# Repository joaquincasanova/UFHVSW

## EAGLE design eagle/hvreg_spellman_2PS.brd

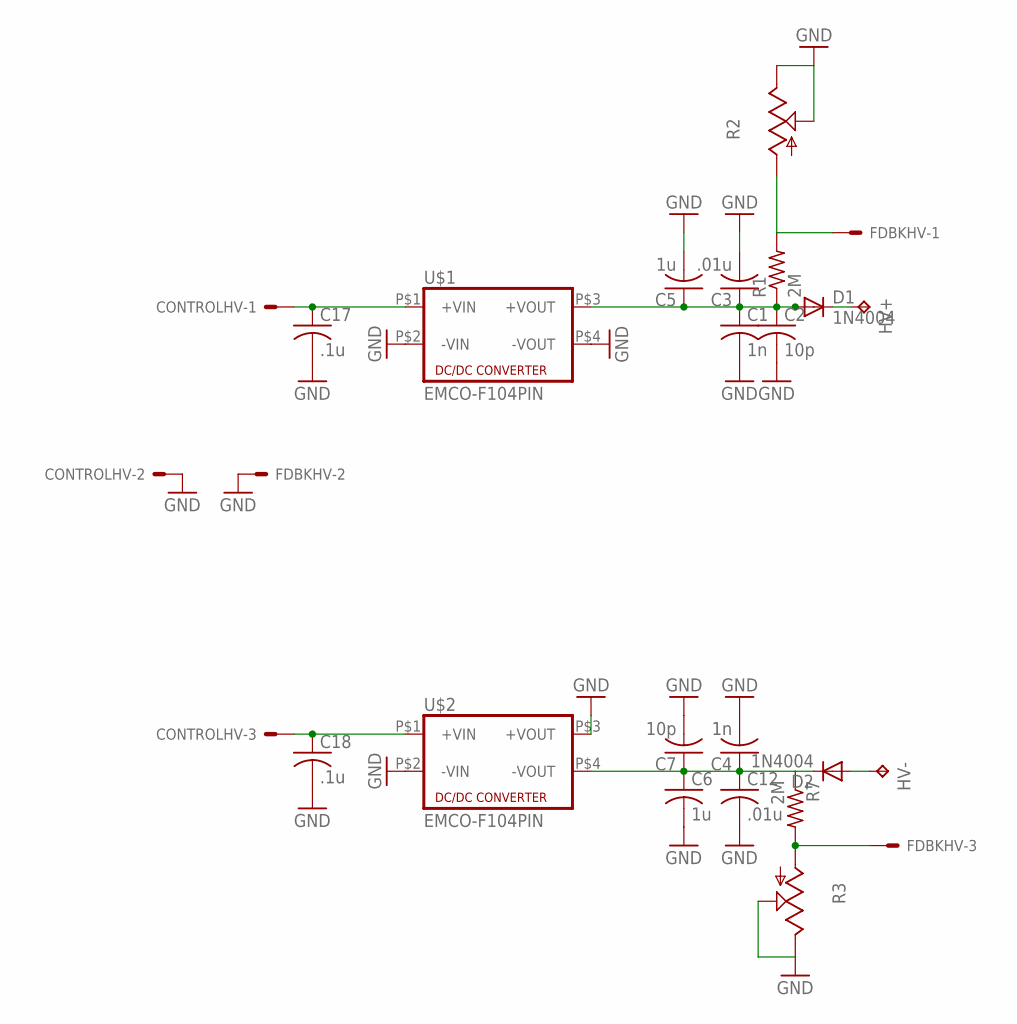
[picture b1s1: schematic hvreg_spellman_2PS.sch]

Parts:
C1, C4: 1n; C102-043X133
C2, C7: 10p; C102-043X133
C3, C12: .01u; C102-043X133
C5, C6: 1u; C275-205X316
C17, C18: .1u; C225-113X268
CONTROLHV: KK-156-3
D1, D2: 1N4004; DO41-10
FDBKHV: KK-156-3
HV+: TPPAD1-20Y; P1-20Y
HV-: TPPAD1-20Y; P1-20Y
R1, R7: 2M; P0613/15
R2, R3: TRIM_US-B90P; SP19L
U$1, U$2: EMCO-F104PIN; EMCO-F

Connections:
GND: C1.2, C2.2, C3.2, C4.2, C5.2, C6.2, C7.2, C12.2, C17.2, C18.2, CONTROLHV.2, FDBKHV.2, R2.E, R2.S, R3.E, R3.S, U$1.P$2 (-VIN), U$1.P$4 (-VOUT), U$2.P$2 (-VIN), U$2.P$3 (+VOUT)
unnamed: C1.1, C2.1, C3.1, C5.1, D1.A, R1.1, U$1.P$3 (+VOUT)
unnamed: C4.1, C6.1, C7.1, C12.1, D2.C, R7.1, U$2.P$4 (-VOUT)
unnamed: FDBKHV.1, R1.2, R2.A
unnamed: D2.A, HV-.TP
unnamed: D1.C, HV+.TP
unnamed: FDBKHV.3, R3.A, R7.2
unnamed: C17.1, CONTROLHV.1, U$1.P$1 (+VIN)
unnamed: C18.1, CONTROLHV.3, U$2.P$1 (+VIN)

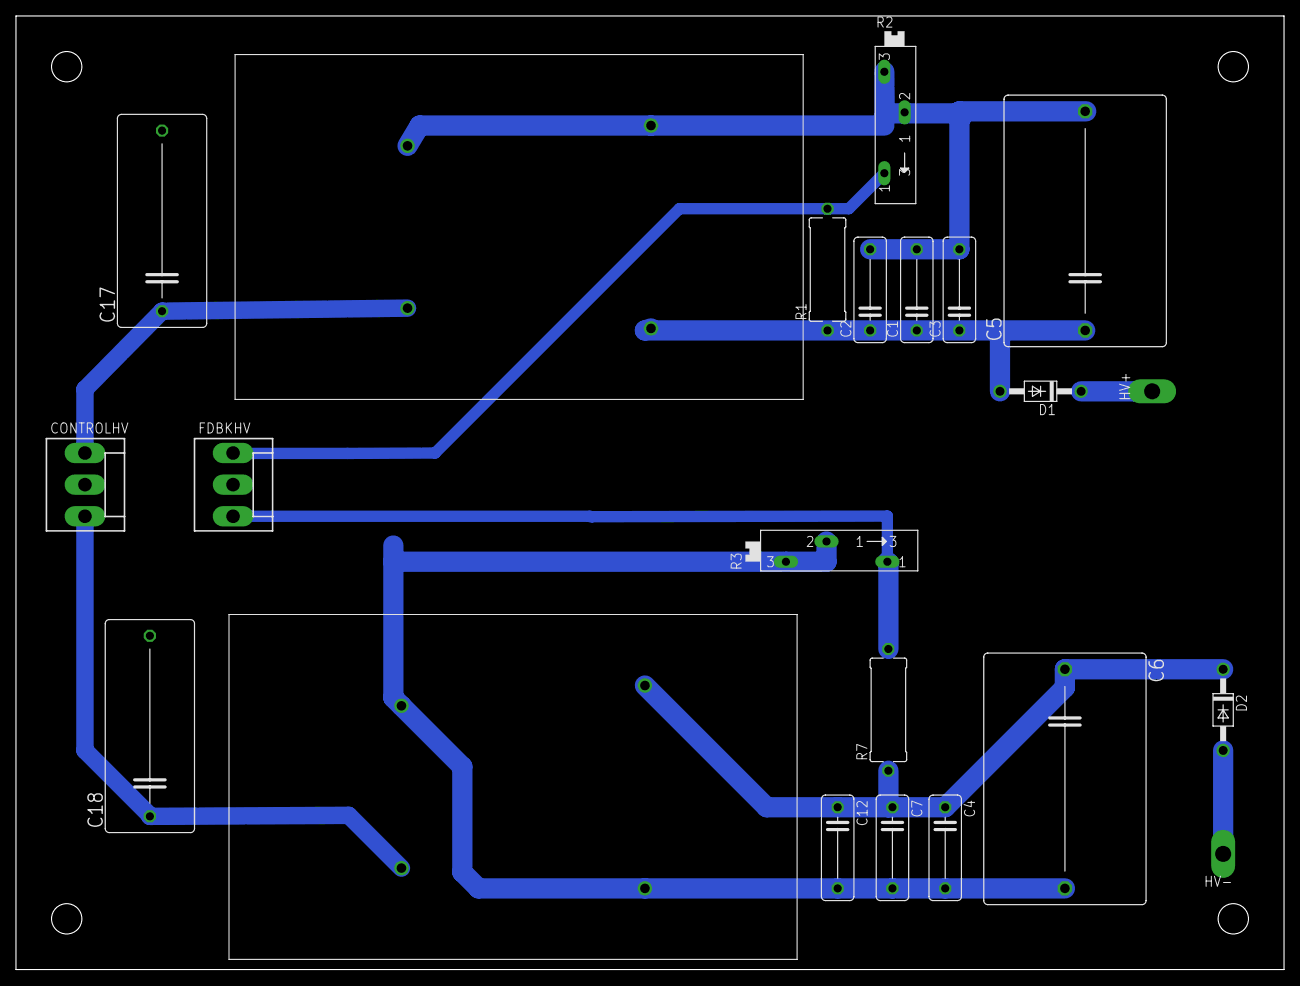
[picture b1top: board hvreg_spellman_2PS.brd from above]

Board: 2 copper layers, 158.8 x 119.4 mm, 22 parts (0 on the bottom side), 9 nets.

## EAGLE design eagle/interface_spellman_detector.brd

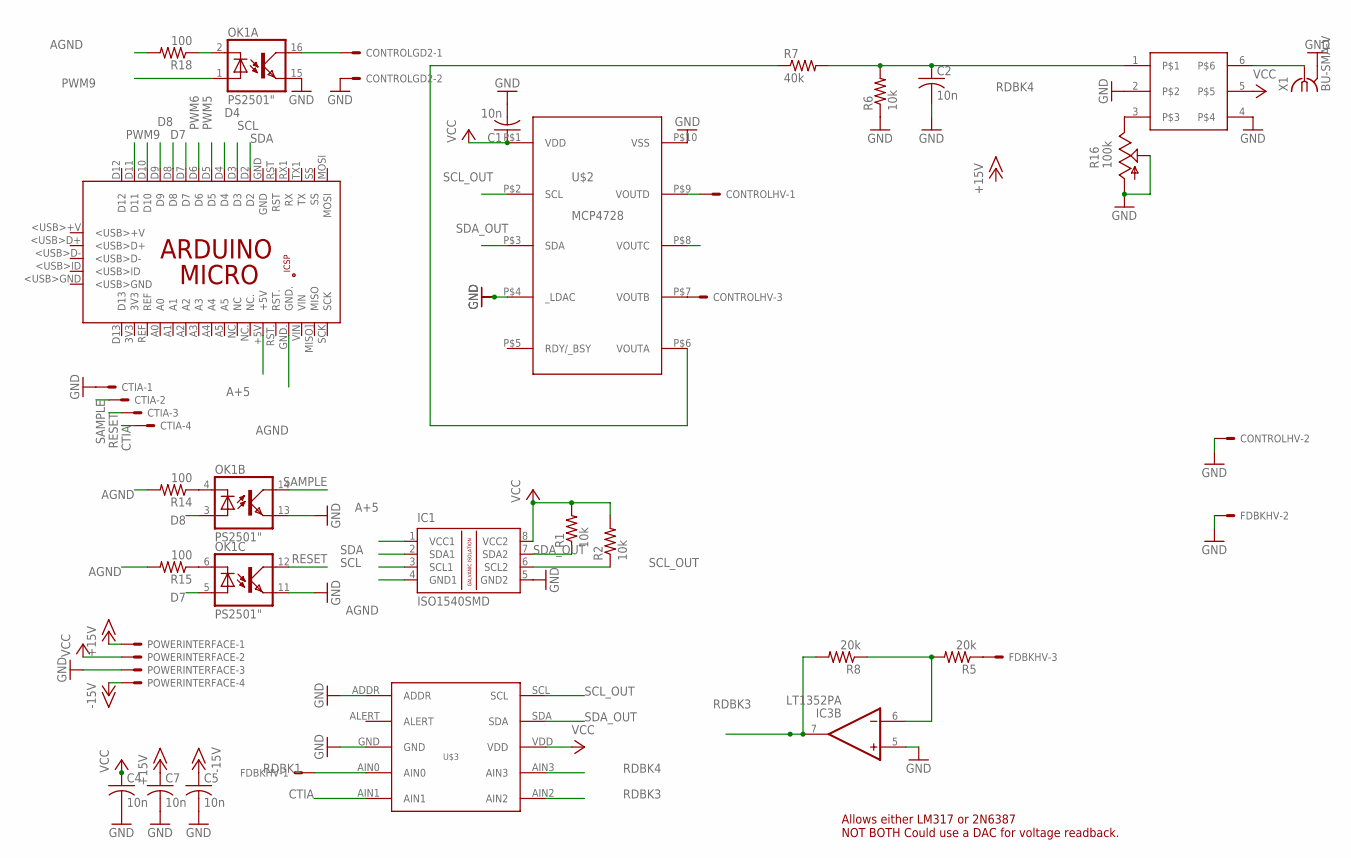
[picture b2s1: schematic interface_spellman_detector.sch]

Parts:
C1, C2, C4, C5, C7: 10n; C0805K
CONTROLGD2: KK-156-2
CONTROLHV: KK-156-3
CTIA: KK-156-4
FDBKHV: KK-156-3
IC1: ISO1540SMD; SOIC8
IC3: LT1352PA; DIL08
OK1: PS2501"; DIL16
PCB1: ARDUINO_MICRO
POWERINTERFACE: KK-156-4
R1, R2, R6: 10k; R0805
R5, R8: 20k; R0805
R7: 40k; R0805
R14, R15, R18: 100; R0805
R16: 100k; B64Y
U$1: LTC6992SMD; SOT23-6
U$2: MCP4728; MSOP-10
U$3: ADS1015; VSOP-10
X1: BU-SMA-V

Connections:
+15V: C7.1, POWERINTERFACE.1
-15V: C5.1, POWERINTERFACE.4
A+5: IC1.1 (VCC1), PCB1.+5V
AGND: IC1.4 (GND1), PCB1.GND., R14.2, R15.2, R18.2
CTIA: CTIA.4, U$3.AIN1
D4: PCB1.D4
D7: OK1.5 (A), PCB1.D7
D8: OK1.3 (A), PCB1.D8
D10: PCB1.D10
D11: PCB1.D11
ENSW2: CONTROLGD2.1, OK1.16 (COL)
GND: C1.2, C2.2, C4.2, C5.2, C7.2, CONTROLGD2.2, CONTROLHV.2, CTIA.1, FDBKHV.2, IC1.5 (GND2), IC3.5 (+IN), OK1.11 (EMI), OK1.13 (EMI), OK1.15 (EMI), POWERINTERFACE.3, R6.1, R16.A, R16.S, U$1.2, U$1.4, U$2.P$4 (_LDAC), U$2.P$10 (VSS), U$3.ADDR, U$3.GND, X1.2, X1.3 (2), X1.4 (2), X1.5 (2)
unnamed: R7.1, U$2.P$6 (VOUTA)
unnamed: OK1.4 (C), R14.1
unnamed: CONTROLHV.3, U$2.P$7 (VOUTB)
unnamed: OK1.6 (C), R15.1
unnamed: OK1.2 (C), R18.1
unnamed: FDBKHV.3, R5.1
unnamed: R16.E, U$1.3
unnamed: U$1.6, X1.1
unnamed: IC3.6 (-IN), R5.2, R8.1
unnamed: CONTROLHV.1, U$2.P$9 (VOUTD)
PWM5: PCB1.D5
PWM6: PCB1.D6
PWM9: OK1.1 (A), PCB1.D9
RDBK1: FDBKHV.1, U$3.AIN0
RDBK3: IC3.7 (OUT), R8.2, U$3.AIN2
RDBK4: C2.1, R6.2, R7.2, U$1.1, U$3.AIN3
RESET: CTIA.3, OK1.12 (COL)
SAMPLE: CTIA.2, OK1.14 (COL)
SCL: IC1.3 (SCL1), PCB1.D3
SCL_OUT: IC1.6 (SCL2), R2.1, U$2.P$2 (SCL), U$3.SCL
SDA: IC1.2 (SDA1), PCB1.D2
SDA_OUT: IC1.7 (SDA2), R1.1, U$2.P$3 (SDA), U$3.SDA
V+: IC3.8 (V+)
V-: IC3.4 (V-)
VCC: C1.1, C4.1, IC1.8 (VCC2), POWERINTERFACE.2, R1.2, R2.2, U$1.5, U$2.P$1 (VDD), U$3.VDD

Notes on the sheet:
Allows either LM317 or 2N6387 NOT BOTH Could use a DAC for voltage readback.

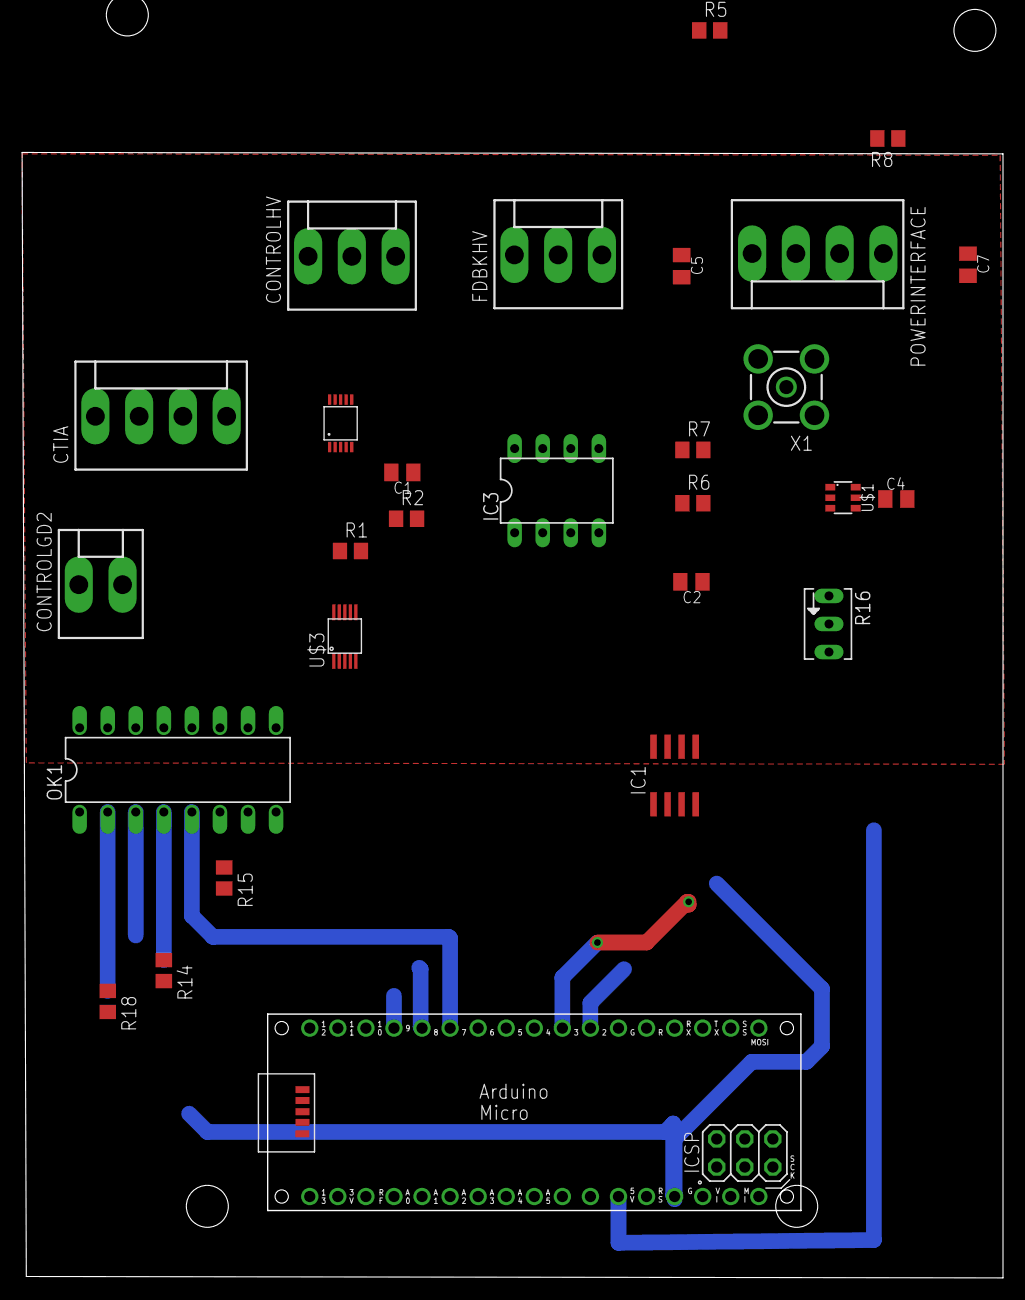
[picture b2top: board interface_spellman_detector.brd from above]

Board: 2 copper layers, 88.8 x 101.9 mm, 28 parts (0 on the bottom side), 30 nets.

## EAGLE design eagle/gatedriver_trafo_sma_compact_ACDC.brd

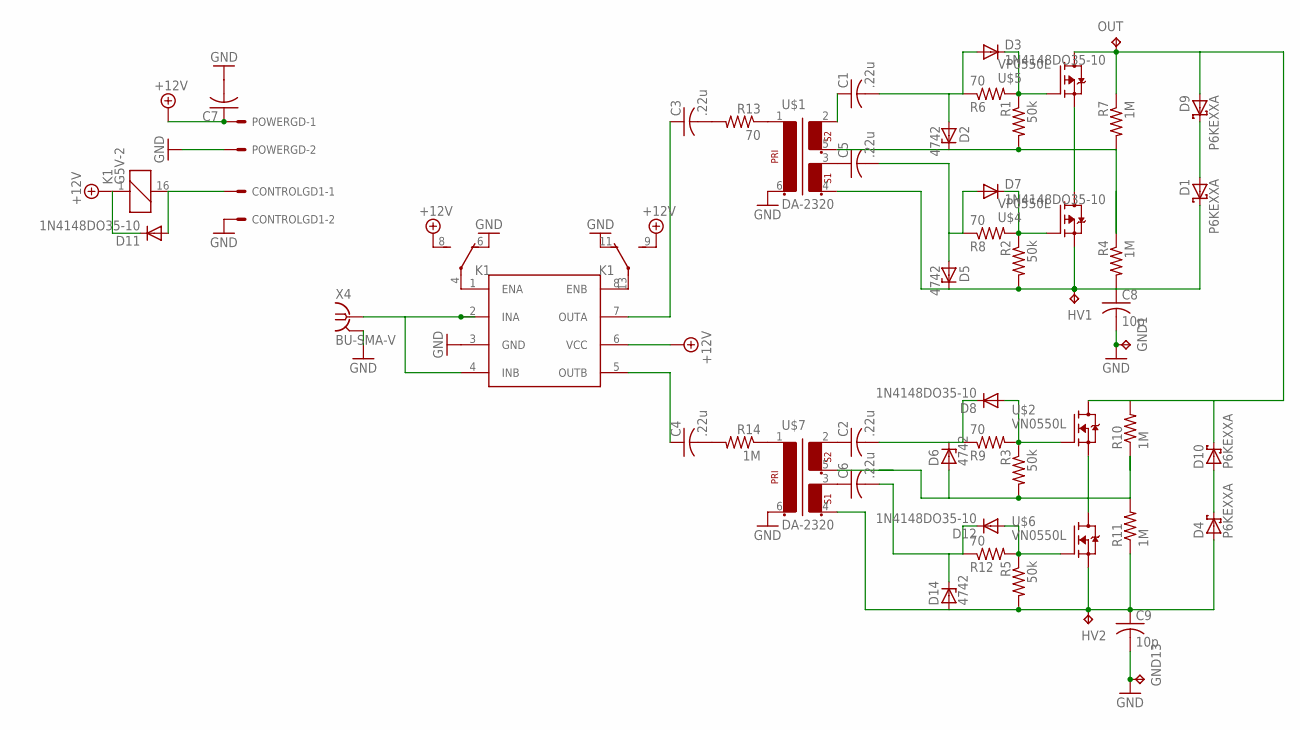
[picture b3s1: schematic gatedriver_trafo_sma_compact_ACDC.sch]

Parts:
C1, C2, C3, C4, C5, C6: .22u; C050-055X075
C7: C-US050-030X075; C050-030X075
C8, C9: 10p; C102-064X133
CONTROLGD1: KK-156-2
D1, D4, D9, D10: P6KEXXA; C1702-15
D2, D5, D6, D14: 4742; ZDIO-10
D3, D7, D8, D11, D12: 1N4148DO35-10; DO35-10
GND1, GND13: TPPAD1-20Y; P1-20Y
HV1, HV2: TPPAD1-20Y; P1-20Y
K1: G5V-2
OUT: TPPAD1-20Y; P1-20Y
POWERGD: KK-156-2
R1, R2, R3, R5: 50k; 0207/10
R4, R7, R10, R11, R14: 1M; 0207/10
R6, R8, R9, R12, R13: 70; 0207/10
U$1, U$7: DA-2320; DIL06
U$2, U$6: VN0550L; TO92L
U$3: UCC27425; DIL08
U$4, U$5: VP0550L; TO92L
X4: BU-SMA-V

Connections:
+15V: C7.1, D11.C, K1.1, K1.8 (S), K1.9 (S), POWERGD.1, U$3.6 (VCC)
ENSW: CONTROLGD1.1, D11.A, K1.16 (2)
GND: C7.2, C8.2, C9.2, CONTROLGD1.2, GND1.TP, GND13.TP, K1.6 (O), K1.11 (O), POWERGD.2, U$1.6 (2), U$3.3 (GND), U$7.6 (2), X4.2, X4.3 (2), X4.4 (2), X4.5 (2)
unnamed: U$3.2 (INA), U$3.4 (INB), X4.1
unnamed: C3.1, U$3.7 (OUTA)
unnamed: R13.1, U$1.1
unnamed: C4.1, U$3.5 (OUTB)
unnamed: C1.1, U$1.2 (6)
unnamed: R14.1, U$7.1
unnamed: C5.1, U$1.3 (4)
unnamed: D3.C, R1.1, R6.2, U$5.2 (G)
unnamed: C1.2, D2.A, D3.A, R6.1
unnamed: D12.A, R5.1, R12.2, U$6.2 (G)
unnamed: D7.C, R2.1, R8.2, U$4.2 (G)
unnamed: D6.A, R3.2, R10.1, R11.2, U$2.3 (S), U$6.1 (D)
unnamed: K1.4, U$3.1 (ENA)
unnamed: K1.13, U$3.8 (ENB)
unnamed: C5.2, D5.A, D7.A, R8.1
unnamed: C8.1, D1.C, D5.C, HV1.TP, R2.2, R4.2, U$1.4 (3), U$4.3 (S)
unnamed: D2.C, R1.2, R4.1, R7.2, U$1.5, U$4.1 (D), U$5.3 (S)
unnamed: C3.2, R13.2
unnamed: C4.2, R14.2
unnamed: D9.A, D10.C, OUT.TP, R7.1, R10.2, U$2.1 (D), U$5.1 (D)
unnamed: C2.1, U$7.2 (6)
unnamed: C6.1, U$7.3 (4)
unnamed: C9.1, D4.A, D14.A, HV2.TP, R5.2, R11.1, U$6.3 (S), U$7.4 (3)
unnamed: C2.2, D6.C, D8.C, R9.1
unnamed: D1.A, D9.C
unnamed: C6.2, D12.C, D14.C, R12.1
unnamed: D4.C, D10.A
unnamed: D8.A, R3.1, R9.2, U$2.2 (G)

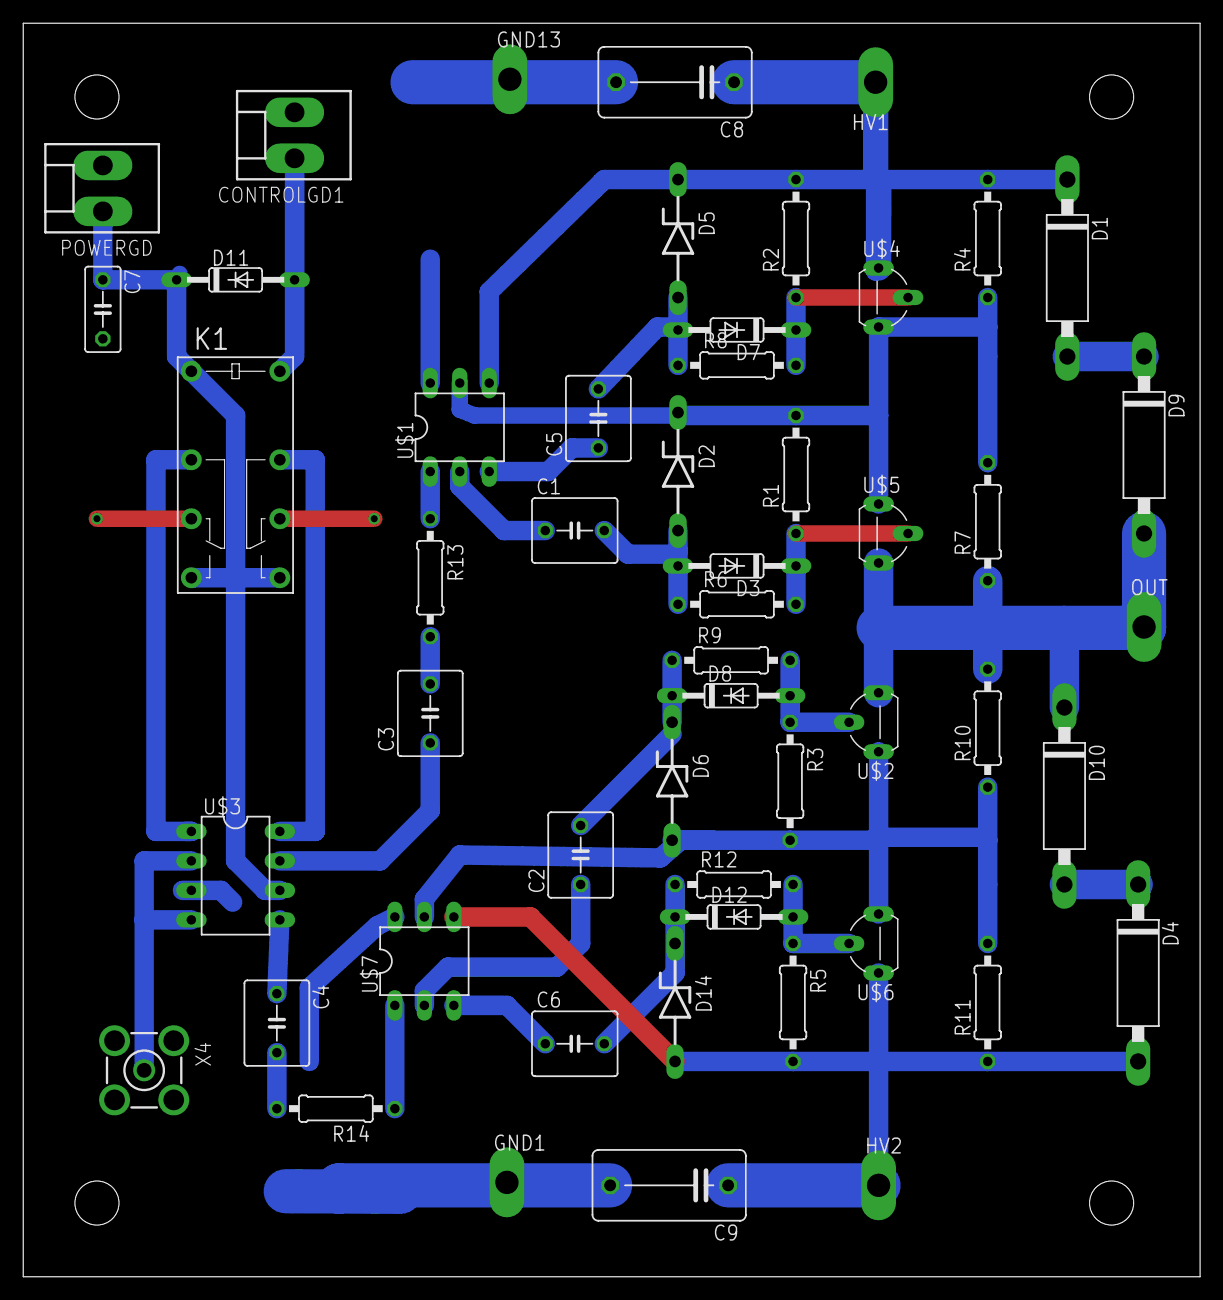
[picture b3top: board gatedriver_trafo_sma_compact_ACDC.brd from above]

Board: 2 copper layers, 101.3 x 108.0 mm, 52 parts (0 on the bottom side), 31 nets.

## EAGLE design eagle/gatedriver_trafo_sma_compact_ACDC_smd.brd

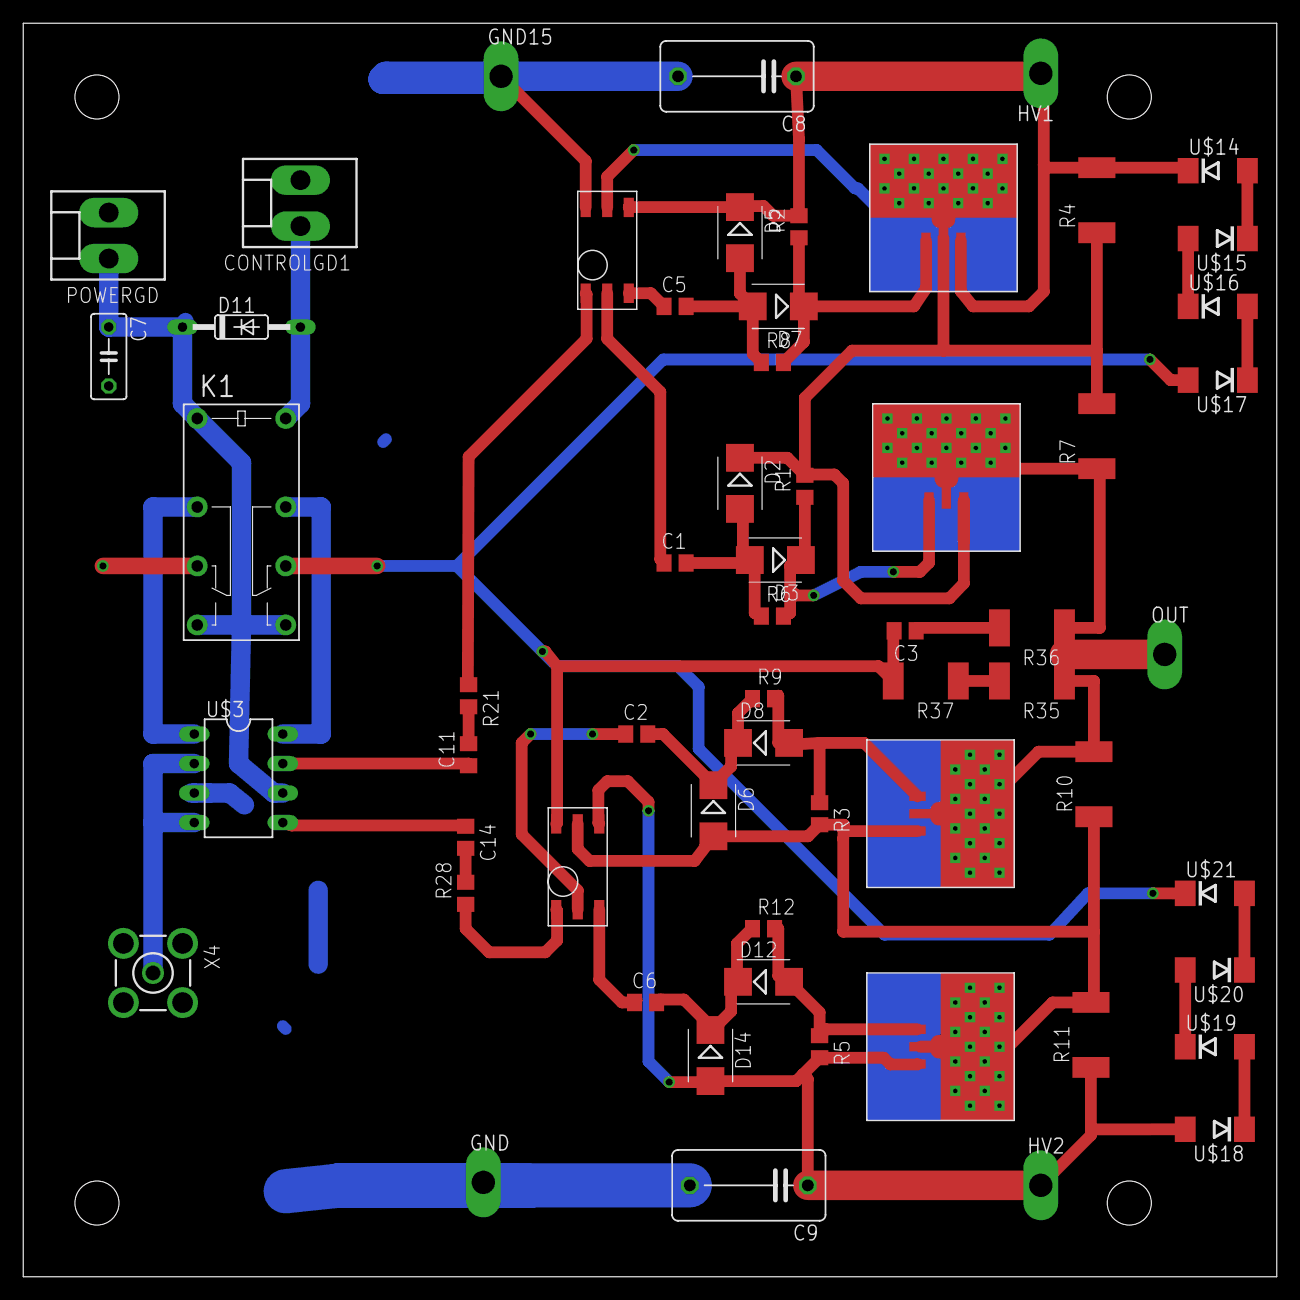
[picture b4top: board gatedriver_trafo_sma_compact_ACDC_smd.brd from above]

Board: 2 copper layers, 108.0 x 108.0 mm, 60 parts (0 on the bottom side), 37 nets.

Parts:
C1, C2, C5, C6, C11, C14: 1u; C0805
C3: 10n; C0805
C7: 10n; C050-030X075
C8, C9: 10p; C102-064X133
CONTROLGD1: KK-156-2
D2, D5, D6, D14: 1SMB5918BT3G; SMB
D3, D7, D8, D12: SMB
D11: 1N4148DO35-10; DO35-10
GND, GND15: TPPAD1-20Y; P1-20Y
HV1, HV2: TPPAD1-20Y; P1-20Y
K1: G5V-2
OUT: TPPAD1-20Y; P1-20Y
POWERGD: KK-156-2
R1, R2, R3, R5: 100k; R0805
R4, R7, R10, R11, R35, R36, R37: 10M; R2512
R6, R8, R9, R12, R21, R28: 10; R0805
U$1, U$7: DA-2320SMD6; SMD6
U$2, U$6: VN2450HS; SO89_HS
U$3: UCC27425; DIL08
U$4, U$5: VP2450HS; SO89_HS
U$14, U$15, U$16, U$17, U$18, U$19, U$20, U$21: SMBJ170D-M3/H; DO214AA
X4: BU-SMA-V

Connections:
+15V: C7.1, D11.C, K1.1, K1.8, K1.9, POWERGD.1, U$3.6
ENSW: CONTROLGD1.1, D11.A, K1.16
GND: C3.2, C7.2, C8.2, C9.2, CONTROLGD1.2, GND.TP, GND15.TP, K1.6, K1.11, POWERGD.2, R37.2, U$1.P$6, U$3.3, U$7.P$6, U$17.A, U$21.C, X4.2, X4.3, X4.4, X4.5
unnamed: U$3.2, U$3.4, X4.1
unnamed: C11.1, U$3.7
unnamed: C14.1, U$3.5
unnamed: C1.1, U$1.P$2
unnamed: C8.1, D5.C, HV1.TP, R2.2, R4.2, U$1.P$4, U$4.E, U$14.C
unnamed: C5.1, U$1.P$3
unnamed: D3.C, R1.1, R6.2, U$5.B
unnamed: D2.C, R1.2, R4.1, R7.2, U$1.P$5, U$4.C, U$4.C@1, U$5.E
unnamed: C1.2, D2.A, D3.A, R6.1
unnamed: D12.A, R5.1, R12.2, U$6.B
unnamed: D7.C, R2.1, R8.2, U$4.B
unnamed: K1.4, U$3.1
unnamed: K1.13, U$3.8
unnamed: C5.2, D5.A, D7.A, R8.1
unnamed: OUT.TP, R7.1, R10.2, R35.1, R36.1, U$2.C, U$2.C@1, U$5.C, U$5.C@1
unnamed: D6.A, R3.2, R10.1, R11.2, U$2.E, U$6.C, U$6.C@1, U$7.P$5
unnamed: C2.1, U$7.P$2
unnamed: C6.1, U$7.P$3
unnamed: C2.2, D6.C, D8.C, R9.1
unnamed: C6.2, D12.C, D14.C, R12.1
unnamed: C9.1, D14.A, HV2.TP, R5.2, R11.1, U$6.E, U$7.P$4, U$18.A
unnamed: R21.1, U$1.P$1
unnamed: C11.2, R21.2
unnamed: C3.1, R36.2
unnamed: R35.2, R37.1
unnamed: U$14.A, U$15.C
unnamed: R28.1, U$7.P$1
unnamed: C14.2, R28.2
unnamed: U$15.A, U$16.C
unnamed: U$16.A, U$17.C
unnamed: U$18.C, U$19.A
unnamed: U$19.C, U$20.A
unnamed: U$20.C, U$21.A
unnamed: D8.A, R3.1, R9.2, U$2.B

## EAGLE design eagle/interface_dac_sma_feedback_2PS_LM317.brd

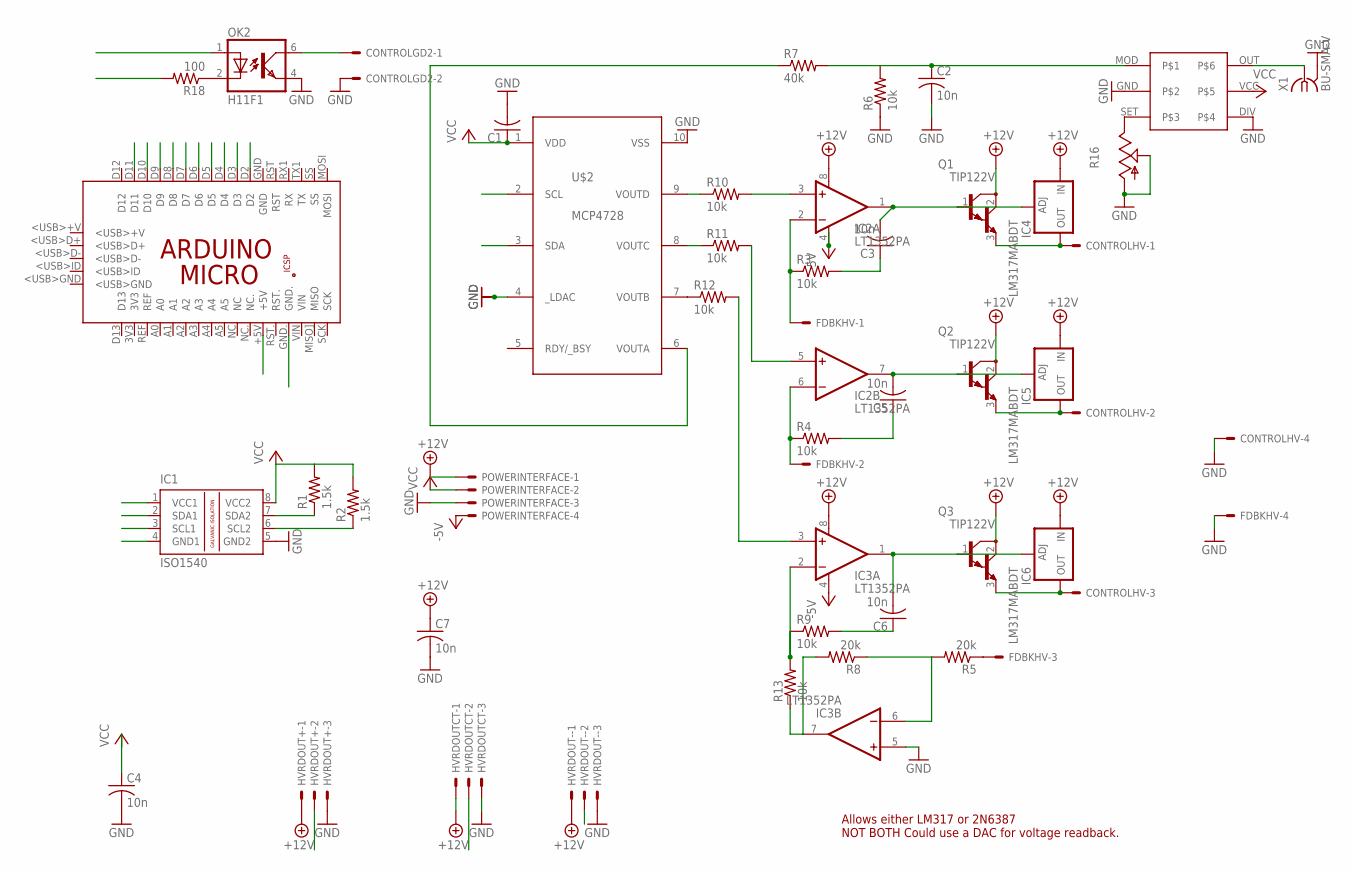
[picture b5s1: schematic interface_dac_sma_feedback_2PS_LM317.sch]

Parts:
C1: C-US050-050X075; C050-050X075
C2, C3, C5, C6: 10n; C050-024X044
C4: 10n; C075-063X106
C7: 10n; C050-050X075
CONTROLGD2: KK-156-2
CONTROLHV: KK-156-4
FDBKHV: KK-156-4
HVRDOUT+: KK-156-3
HVRDOUT-: KK-156-3
HVRDOUTCT: KK-156-3
IC1: ISO1540; DIL08
IC2, IC3: LT1352PA; DIL08
IC4, IC5, IC6: LM317MABDT; DPACK
OK2: H11F1; DIL05
PCB1: ARDUINO_MICRO
POWERINTERFACE: KK-156-4
Q1, Q2, Q3: TIP122V; TO220V
R1, R2: 1.5k; 0207/12
R3, R4, R6, R9, R10, R11, R12, R13: 10k; 0207/12
R5, R8: 20k; 0207/12
R7: 40k; 0207/12
R16: TRIM_US-B90P; SP19L
R18: 100; 0207/12
U$1: LTC6992; DIL06
U$2: MCP4728DIL; DIL10
X1: BU-SMA-V

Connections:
+12V: C7.1, HVRDOUT+.1, HVRDOUT-.1, HVRDOUTCT.1, IC2.8 (V+), IC3.8 (V+), IC4.3 (IN), IC5.3 (IN), IC6.3 (IN), POWERINTERFACE.1, Q1.2 (C), Q2.2 (C), Q3.2 (C)
-5V: IC2.4 (V-), IC3.4 (V-), POWERINTERFACE.4
A+5: IC1.1 (VCC1), PCB1.+5V
AGND: IC1.4 (GND1), PCB1.GND., R18.2
D4: PCB1.D4
D7: PCB1.D7
D8: PCB1.D8
D10: PCB1.D10
D11: PCB1.D11
ENSW2: CONTROLGD2.1, OK2.6 (COL)
GND: C1.2, C2.2, C4.2, C7.2, CONTROLGD2.2, CONTROLHV.4, FDBKHV.4, HVRDOUT+.3, HVRDOUT-.3, HVRDOUTCT.3, IC1.5 (GND2), IC3.5 (+IN), OK2.4 (EMIT), POWERINTERFACE.3, R6.1, R16.A, R16.S, U$1.DIV, U$1.GND, U$2.4 (_LDAC), U$2.10 (VSS), X1.2, X1.3 (2), X1.4 (2), X1.5 (2)
unnamed: R7.1, U$2.6 (VOUTA)
unnamed: C2.1, R6.2, R7.2, U$1.MOD
unnamed: C3.1, R3.2
unnamed: CONTROLHV.1, IC4.4 (OUT), Q1.3 (E)
unnamed: CONTROLHV.3, IC6.4 (OUT), Q3.3 (E)
unnamed: FDBKHV.2, HVRDOUTCT.2, IC2.6 (-IN), R4.1
unnamed: OK2.2 (C), R18.1
unnamed: FDBKHV.1, HVRDOUT+.2, IC2.2 (-IN), R3.1
unnamed: FDBKHV.3, R5.1
unnamed: C5.2, IC2.7 (OUT), IC5.1 (ADJ), Q2.1 (B)
unnamed: CONTROLHV.2, IC5.4 (OUT), Q2.3 (E)
unnamed: R16.E, U$1.SET
unnamed: U$1.OUT, X1.1
unnamed: HVRDOUT-.2, IC3.7 (OUT), R8.2, R13.1
unnamed: C5.1, R4.2
unnamed: IC2.3 (+IN), R10.2
unnamed: IC2.5 (+IN), R11.2
unnamed: IC3.3 (+IN), R12.2
unnamed: C3.2, IC2.1 (OUT), IC4.1 (ADJ), Q1.1 (B)
unnamed: C6.1, R9.2
unnamed: C6.2, IC3.1 (OUT), IC6.1 (ADJ), Q3.1 (B)
unnamed: IC3.6 (-IN), R5.2, R8.1
unnamed: R10.1, U$2.9 (VOUTD)
unnamed: R12.1, U$2.7 (VOUTB)
unnamed: R11.1, U$2.8 (VOUTC)
unnamed: IC3.2 (-IN), R9.1, R13.2
PWM5: PCB1.D5
PWM6: PCB1.D6
PWM9: OK2.1 (A), PCB1.D9
SCL: IC1.3 (SCL1), PCB1.D3
SCL_OUT: IC1.6 (SCL2), R2.1, U$2.2 (SCL)
SDA: IC1.2 (SDA1), PCB1.D2
SDA_OUT: IC1.7 (SDA2), R1.1, U$2.3 (SDA)
VCC: C1.1, C4.1, IC1.8 (VCC2), POWERINTERFACE.2, R1.2, R2.2, U$1.VCC, U$2.1 (VDD)

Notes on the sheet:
Allows either LM317 or 2N6387 NOT BOTH Could use a DAC for voltage readback.

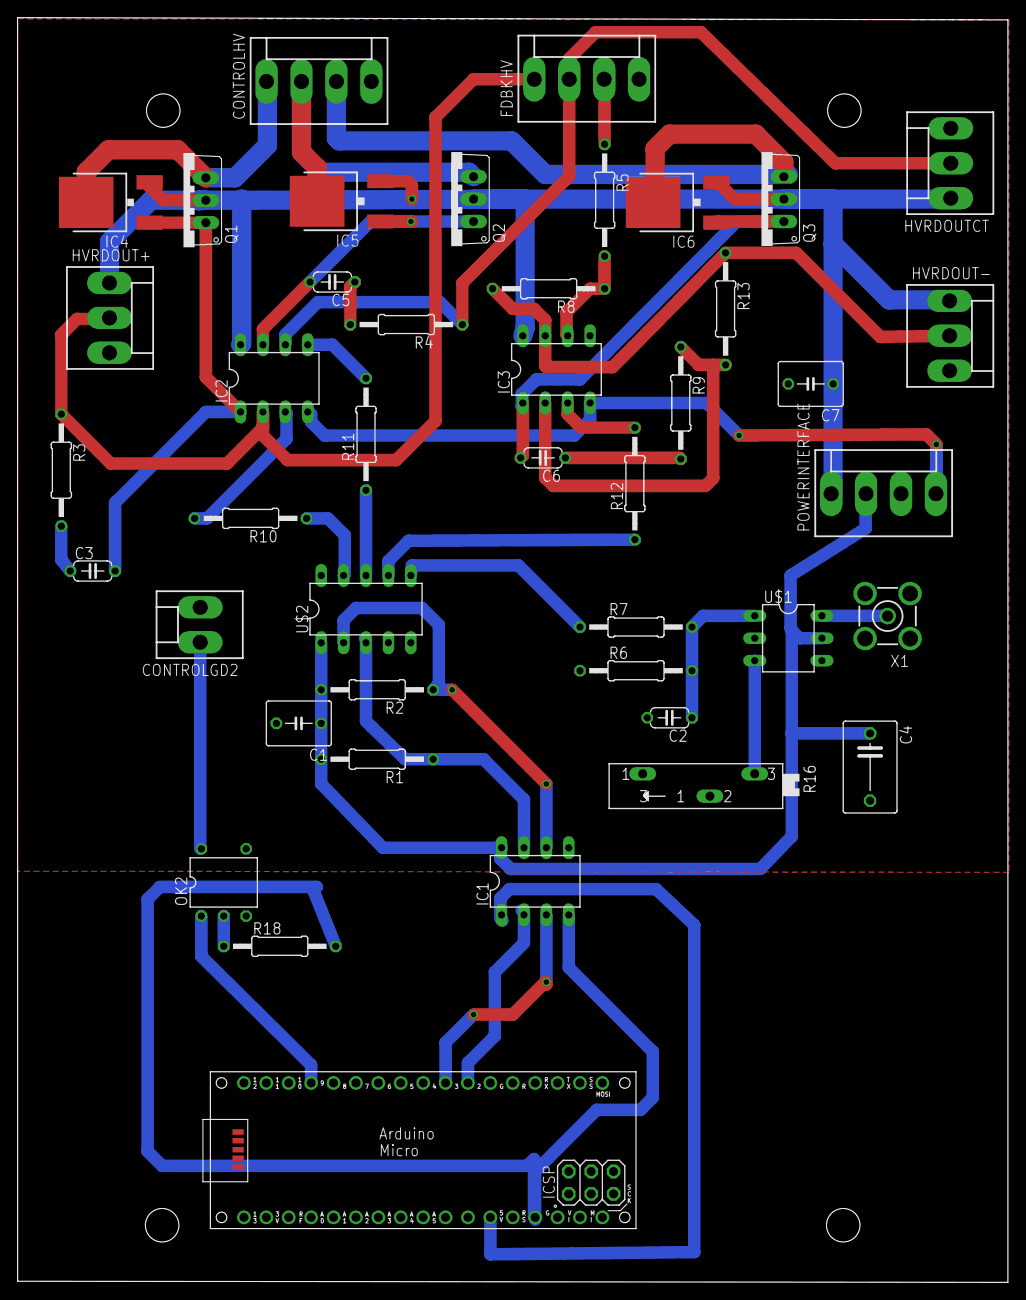
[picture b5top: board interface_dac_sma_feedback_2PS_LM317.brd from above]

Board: 2 copper layers, 112.3 x 143.4 mm, 43 parts (0 on the bottom side), 38 nets.

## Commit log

2015-08-10 :confetti_ball: Added .gitattributes & .gitignore files
2015-08-10 init
2015-08-11 code
2015-08-12 add iso1540
2015-08-14 board tweak
2015-08-18 Board, code for dac
2015-08-21 Code debug, add darlingtons to HV input
2015-08-28 darlington gate resistor, diode stacking
2015-09-04 feedback on hv rails
2015-09-09 use SW on one side, DC on the other. HV feedback. Positive only
2015-09-15 3PS, 2 1kV in parallel
2015-09-18 capacitor bank
2015-09-21 IXYS board solution, gatedriver components
2015-09-22 4pcb upload
2015-10-02 tweaks. still need bigger vias for zeners and hv resistors
2015-10-06 layout fixes
2015-10-13 tweaks - submit to advanced circuits
2015-10-15 use lm317, appropriate opamp resistor selection, ultra gatedriver stacks 4 fets
2015-10-16 two ps in parallel
2015-10-18 ultra layout. try that next time with lm317 interface
2015-10-23 use lt1352 opamp for feedback, smd output up to 1.6kVpp
2015-10-23 more smd changes
2015-10-28 submit smd board
2015-10-30 code streamline. debugging/tuning voltage feedback
2015-11-03 codeine
2015-11-05 update component values
2015-11-10 Update values, code
2015-11-11 Had the wrong trafo footprint! Fixed now
2015-11-11 add tplace trafo
2015-11-16 Fix negative rail problems
2015-11-18 Add cv sweep
2015-11-18 move files around
2015-11-19 mods to include negative mode, warning before start, voltage readout pins
2015-11-19 named proper
2015-11-25 Fix gate driver missing trace, make changes to code for wei
2015-12-01 Component value changes for gate driver with new fets (VN2450)
2015-12-14 optional 317 regulation of emcos
2016-01-08 Readbacks
2016-01-13 Add adc
2016-01-29 Changes for CTIA integration
2016-02-03 code changes for better safety
2016-02-10 update for thermal issues and CTIA breakout
2016-02-16 smd layout, debug code
2016-02-24 add ctia stuff to code
2016-02-29 use 2n3055 for voltage regulation
2016-03-09 gd mods
2016-03-14 hv supply change?
2016-03-18 Square wave one side/dc other
2016-03-23 new twists
2016-03-25 code, simulations, heat sink layout
2016-03-27 Heatsink, CTIA code
2016-03-29 hs/ctia job
2016-04-08 code update for datalogging
2016-04-15 timing ctia
2016-05-18 tweak code - cal factors
